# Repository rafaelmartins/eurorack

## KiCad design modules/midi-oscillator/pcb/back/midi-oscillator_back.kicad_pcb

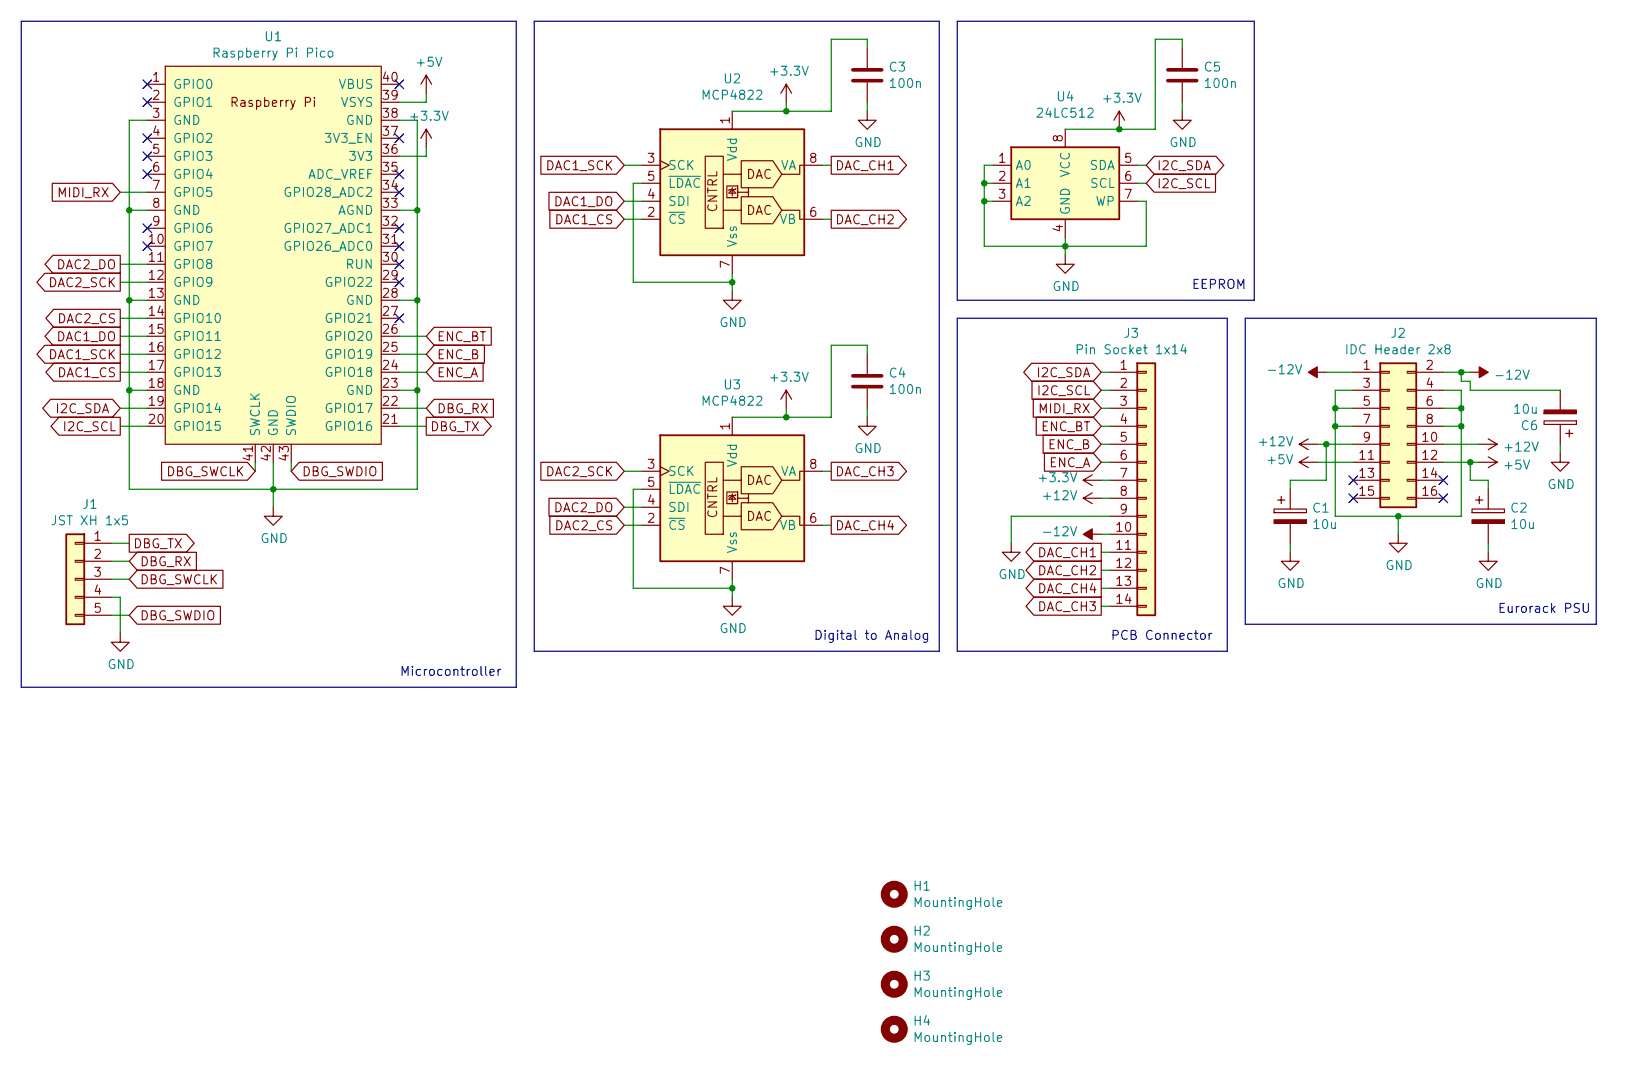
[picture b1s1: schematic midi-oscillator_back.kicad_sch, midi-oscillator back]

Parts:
C1, C2, C6: 10u; CP_Radial_D5.0mm_P2.50mm
C3, C4, C5: 100n; C_Disc_D4.3mm_W1.9mm_P5.00mm
H1, H2, H3, H4: MountingHole; MountingHole_2.2mm_M2
J1: JST XH 1x5; JST_XH_B5B-XH-A_1x05_P2.50mm_Vertical
J2: IDC Header 2x8; IDC-Header_2x08_P2.54mm_Vertical
J3: Pin Socket 1x14; PinSocket_1x14_P2.54mm_Vertical
U1: Raspberry Pi Pico; RPi_Pico_SMD_TH
U2, U3: MCP4822; DIP-8_W7.62mm
U4: 24LC512; DIP-8_W7.62mm

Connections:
+3.3V: C3.1, C4.1, C5.1, J3.7, U1.36 (3V3), U2.1 (Vdd), U3.1 (Vdd), U4.8 (VCC)
+5V: C2.1, J2.11, J2.12, U1.39 (VSYS)
+12V: C1.1, J2.9, J2.10, J3.8
-12V: C6.2, J2.1, J2.2, J3.10
DAC1_CS: U1.17 (GPIO13), U2.2 (~CS)
DAC1_DO: U1.15 (GPIO11), U2.4 (SDI)
DAC1_SCK: U1.16 (GPIO12), U2.3 (SCK)
DAC2_CS: U1.14 (GPIO10), U3.2 (~CS)
DAC2_DO: U1.11 (GPIO8), U3.4 (SDI)
DAC2_SCK: U1.12 (GPIO9), U3.3 (SCK)
DAC_CH1: J3.11, U2.8 (VA)
DAC_CH2: J3.12, U2.6 (VB)
DAC_CH3: J3.14, U3.8 (VA)
DAC_CH4: J3.13, U3.6 (VB)
DBG_RX: J1.2, U1.22 (GPIO17)
DBG_SWCLK: J1.3, U1.41 (SWCLK)
DBG_SWDIO: J1.5, U1.43 (SWDIO)
DBG_TX: J1.1, U1.21 (GPIO16)
ENC_A: J3.6, U1.24 (GPIO18)
ENC_B: J3.5, U1.25 (GPIO19)
ENC_BT: J3.4, U1.26 (GPIO20)
GND: C1.2, C2.2, C3.2, C4.2, C5.2, C6.1, J1.4, J2.3, J2.4, J2.5, J2.6, J2.7, J2.8, J3.9, U1.3 (GND), U1.8 (GND), U1.13 (GND), U1.18 (GND), U1.23 (GND), U1.28 (GND), U1.33 (AGND), U1.38 (GND), U1.42 (GND), U2.5 (~LDAC), U2.7 (Vss), U3.5 (~LDAC), U3.7 (Vss), U4.1 (A0), U4.2 (A1), U4.3 (A2), U4.4 (GND), U4.7 (WP)
I2C_SCL: J3.2, U1.20 (GPIO15), U4.6 (SCL)
I2C_SDA: J3.1, U1.19 (GPIO14), U4.5 (SDA)
MIDI_RX: J3.3, U1.7 (GPIO5)

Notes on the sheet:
EEPROM
PCB Connector
Eurorack PSU
Digital to Analog
Microcontroller

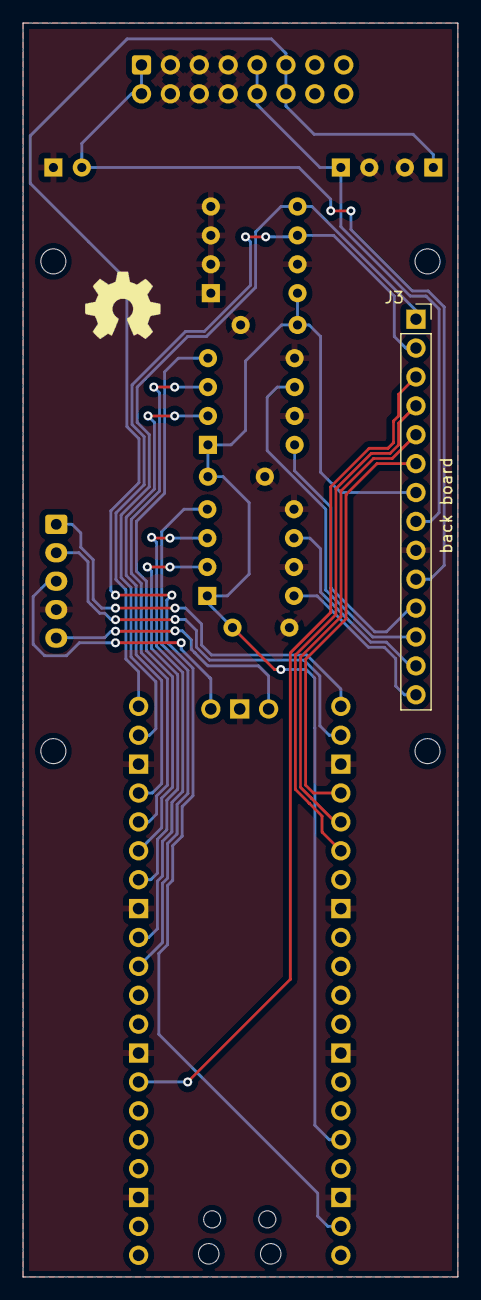
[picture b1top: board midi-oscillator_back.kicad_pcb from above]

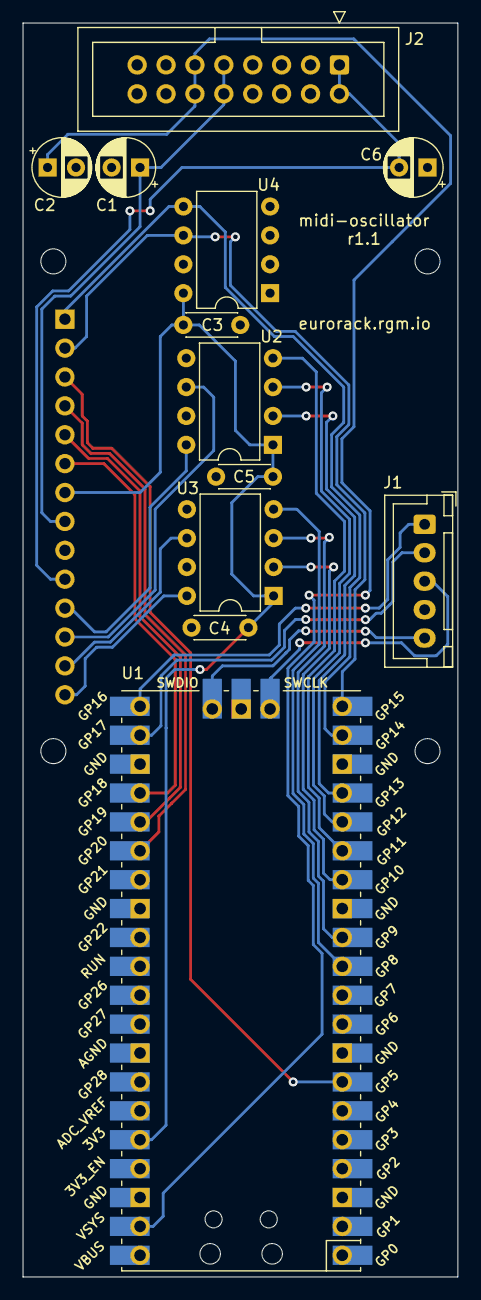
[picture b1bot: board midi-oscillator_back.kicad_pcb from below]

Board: 2 copper layers, 38.2 x 110.2 mm, 17 parts (12 on the bottom side), 25 nets.

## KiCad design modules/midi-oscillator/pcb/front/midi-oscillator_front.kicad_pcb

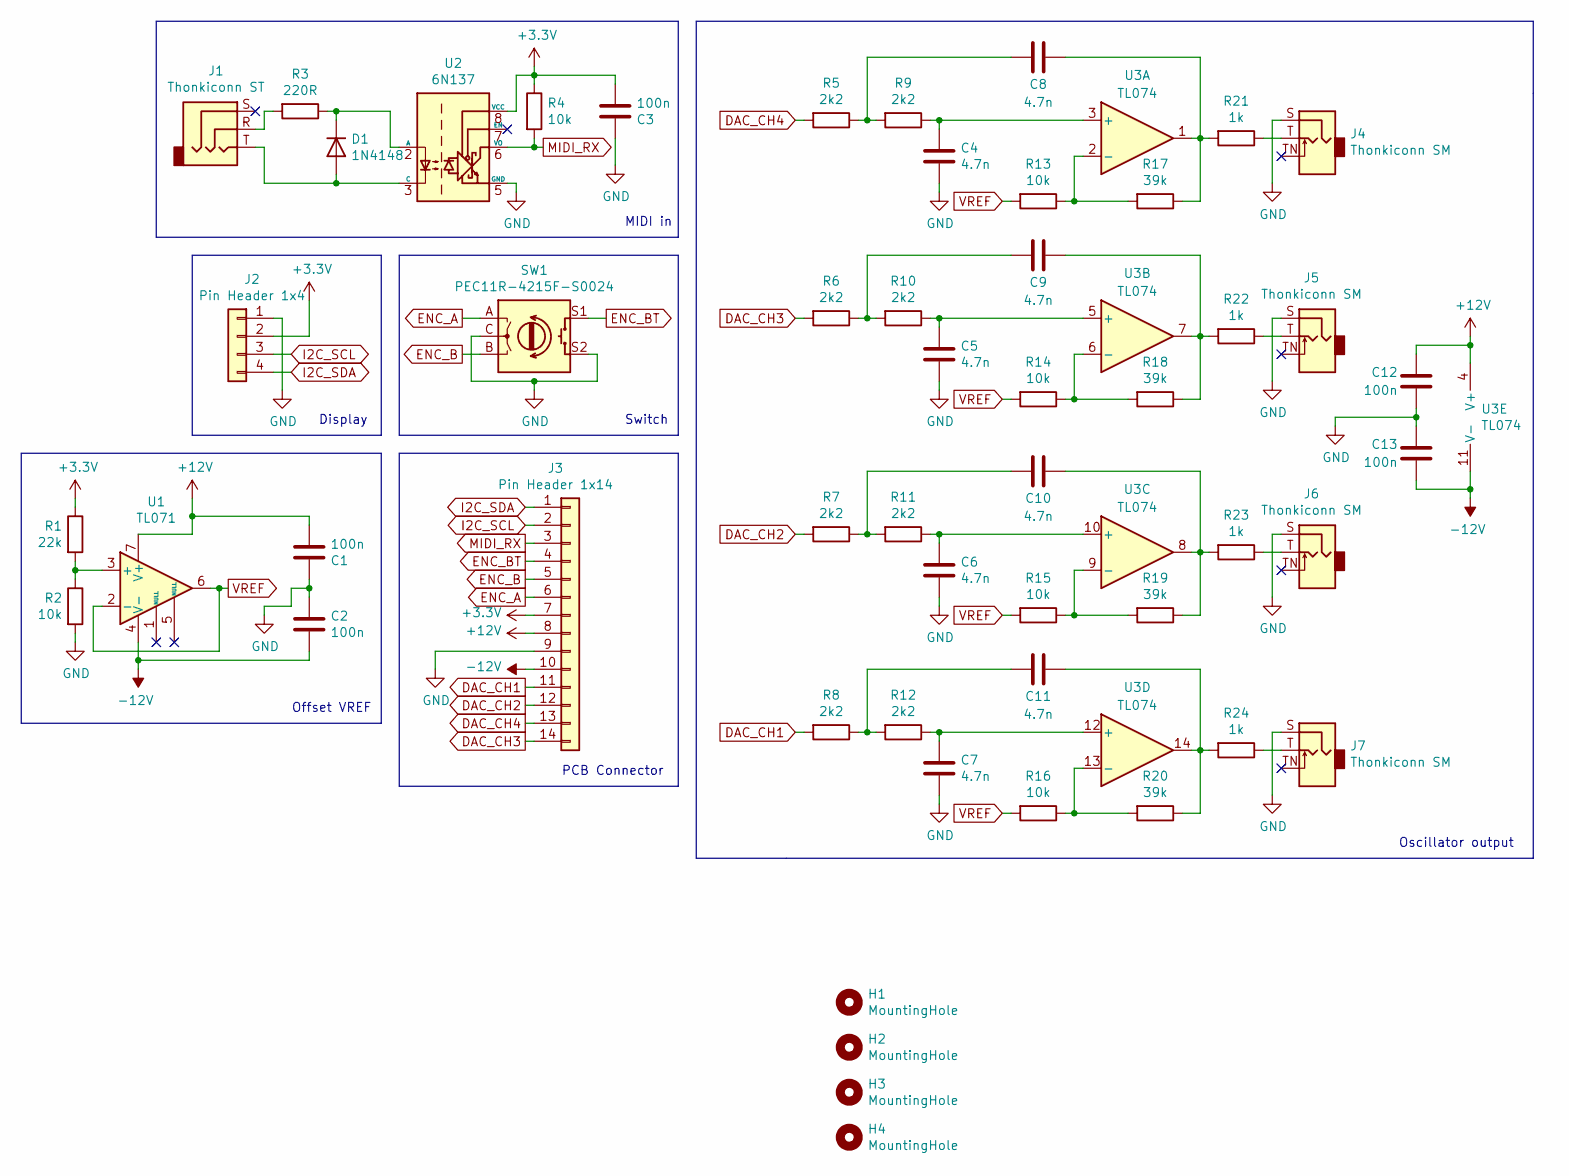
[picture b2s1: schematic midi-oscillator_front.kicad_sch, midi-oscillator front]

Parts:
C1, C2, C3, C12, C13: 100n; C_Disc_D4.3mm_W1.9mm_P5.00mm
C4, C5, C6, C7, C8, C9, C10, C11: 4.7n; C_Rect_L7.0mm_W2.5mm_P5.00mm
D1: 1N4148; D_DO-35_SOD27_P7.62mm_Horizontal
H1, H2, H3, H4: MountingHole; MountingHole_2.2mm_M2
J1: Thonkiconn ST; Jack_3.5mm_QingPu_WQP-PJ366ST_Vertical
J2: Pin Header 1x4; PinSocket_1x04_P2.54mm_Vertical
J3: Pin Header 1x14; PinHeader_1x14_P2.54mm_Vertical
J4, J5, J6, J7: Thonkiconn SM; Jack_3.5mm_QingPu_WQP-PJ398SM_Vertical
R1: 22k; R_Axial_DIN0207_L6.3mm_D2.5mm_P10.16mm_Horizontal
R2, R4, R13, R14, R15, R16: 10k; R_Axial_DIN0207_L6.3mm_D2.5mm_P10.16mm_Horizontal
R3: 220R; R_Axial_DIN0207_L6.3mm_D2.5mm_P10.16mm_Horizontal
R5, R6, R7, R8, R9, R10, R11, R12: 2k2; R_Axial_DIN0207_L6.3mm_D2.5mm_P10.16mm_Horizontal
R17, R18, R19, R20: 39k; R_Axial_DIN0207_L6.3mm_D2.5mm_P10.16mm_Horizontal
R21, R22, R23, R24: 1k; R_Axial_DIN0207_L6.3mm_D2.5mm_P10.16mm_Horizontal
SW1: PEC11R-4215F-S0024; RotaryEncoder_Alps_EC11E-Switch_Vertical_H20mm_CircularMoun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
U1: TL071; DIP-8_W7.62mm
U2: 6N137; DIP-8_W7.62mm
U3: TL074; DIP-14_W7.62mm

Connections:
+3.3V: C3.2, J2.2, J3.7, R1.1, R4.1, U2.8 (VCC)
+12V: C1.2, C12.2, J3.8, U1.7 (V+), U3.4 (V+)
-12V: C2.2, C13.2, J3.10, U1.4 (V-), U3.11 (V-)
DAC_CH1: J3.11, R8.2
DAC_CH2: J3.12, R7.2
DAC_CH3: J3.14, R6.2
DAC_CH4: J3.13, R5.2
ENC_A: J3.6, SW1.A
ENC_B: J3.5, SW1.B
ENC_BT: J3.4, SW1.S1
GND: C1.1, C2.1, C3.1, C4.2, C5.2, C6.2, C7.2, C12.1, C13.1, J2.1, J3.9, J4.S, J5.S, J6.S, J7.S, R2.2, SW1.C, SW1.S2, U2.5 (GND)
I2C_SCL: J2.3, J3.2
I2C_SDA: J2.4, J3.1
MIDI_RX: J3.3, R4.2, U2.6 (VO)
unnamed: C4.1, R9.1, U3.3 (+)
unnamed: C5.1, R10.1, U3.5 (+)
unnamed: C6.1, R11.1, U3.10 (+)
unnamed: C7.1, R12.1, U3.12 (+)
unnamed: C8.1, R5.1, R9.2
unnamed: C8.2, R17.1, R21.2, U3.1
unnamed: C9.1, R6.1, R10.2
unnamed: C9.2, R18.1, R22.2, U3.7
unnamed: C10.1, R7.1, R11.2
unnamed: C10.2, R19.1, R23.2, U3.8
unnamed: C11.1, R8.1, R12.2
unnamed: C11.2, R20.1, R24.2, U3.14
unnamed: D1.1 (K), R3.1, U2.2 (A)
unnamed: D1.2 (A), J1.T, U2.3 (C)
unnamed: J1.R, R3.2
unnamed: J4.T, R21.1
unnamed: J5.T, R22.1
unnamed: J6.T, R23.1
unnamed: J7.T, R24.1
unnamed: R1.2, R2.1, U1.3 (+)
unnamed: R13.1, R17.2, U3.2 (-)
unnamed: R14.1, R18.2, U3.6 (-)
unnamed: R15.1, R19.2, U3.9 (-)
unnamed: R16.1, R20.2, U3.13 (-)
VREF: R13.2, R14.2, R15.2, R16.2, U1.2 (-), U1.6

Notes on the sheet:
Offset VREF
Oscillator output
Switch
Display
PCB Connector
MIDI in

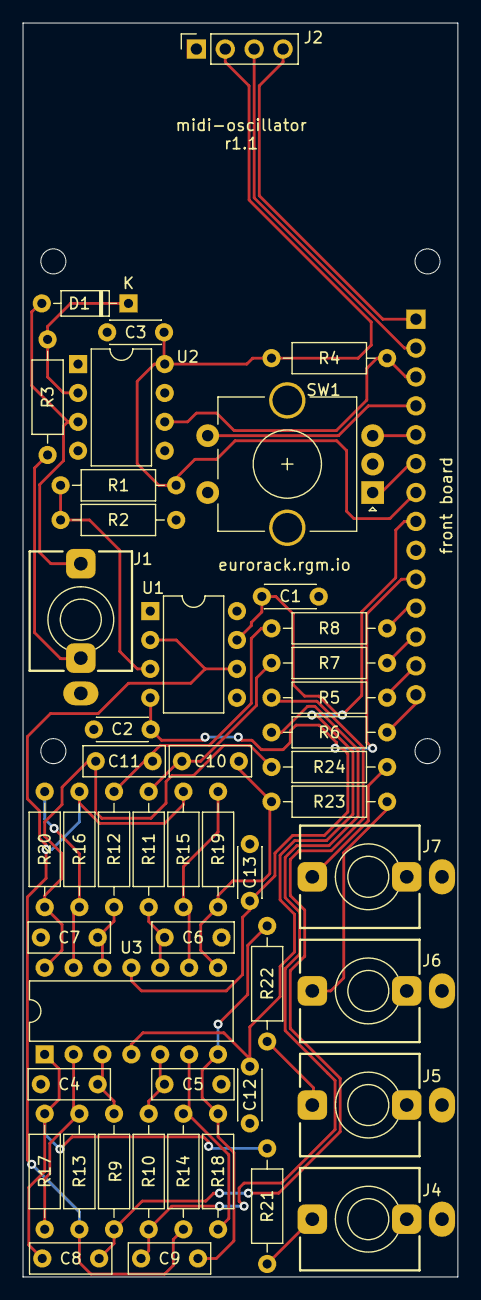
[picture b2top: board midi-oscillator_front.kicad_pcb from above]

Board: 2 copper layers, 38.2 x 110.2 mm, 53 parts (1 on the bottom side), 39 nets.

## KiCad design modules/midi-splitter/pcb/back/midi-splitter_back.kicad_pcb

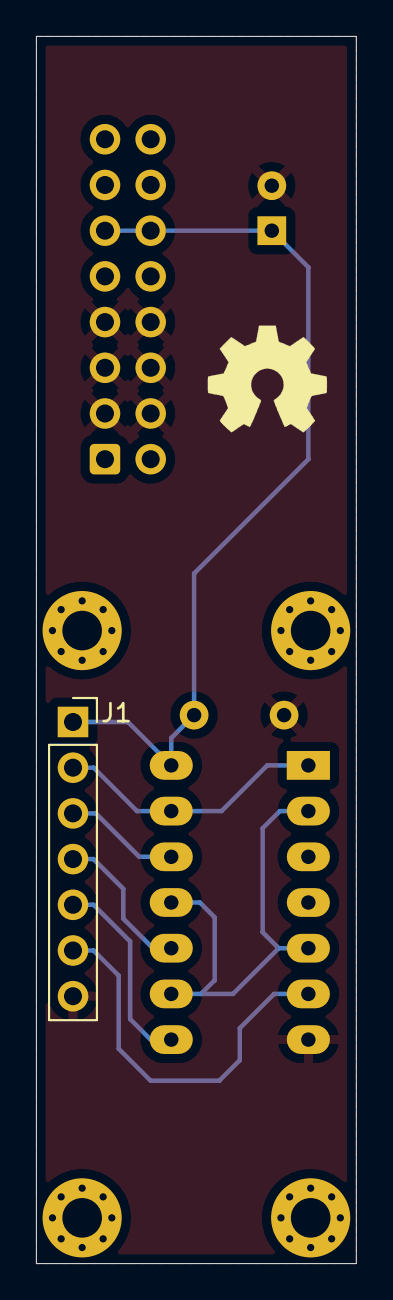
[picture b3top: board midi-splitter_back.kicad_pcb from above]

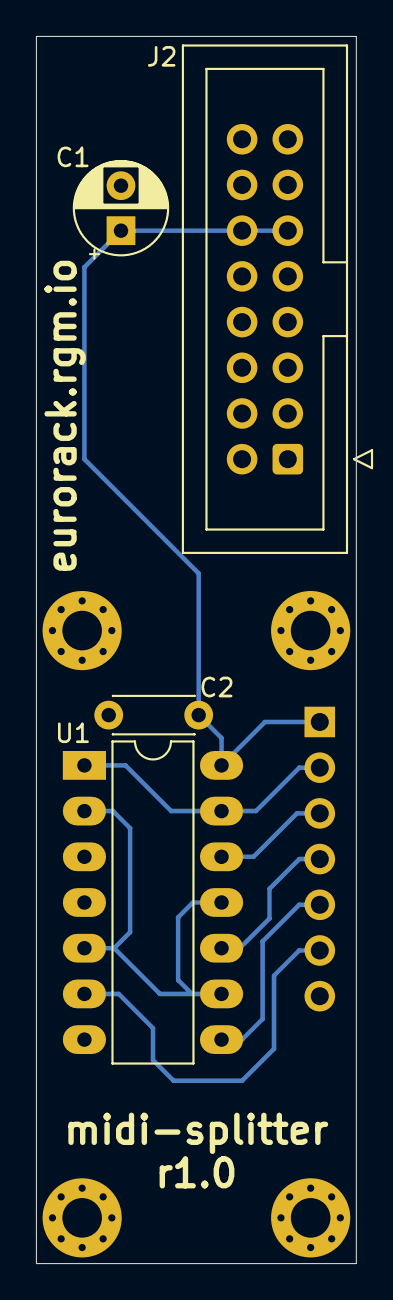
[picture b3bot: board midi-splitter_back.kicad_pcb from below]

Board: 2 copper layers, 17.8 x 68.2 mm, 9 parts (4 on the bottom side), 8 nets.

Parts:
C1: 10u; CP_Radial_D5.0mm_P2.50mm
C2: 100n; C_Disc_D4.3mm_W1.9mm_P5.00mm
H1, H2, H3, H4: MountingHole; MountingHole_2.2mm_M2_Pad_Via
J1: Pin Socket 1x7; PinSocket_1x07_P2.54mm_Vertical
J2: IDC Header 2x8; IDC-Header_2x08_P2.54mm_Vertical
U1: 74HC14; DIP-14_W7.62mm_LongPads

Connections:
+5V: C1.1, C2.1, J1.1, J2.11, J2.12, U1.14 (VCC)
GND: C1.2, C2.2, J1.7, J2.3, J2.4, J2.5, J2.6, J2.7, J2.8, U1.7 (GND)
LED: J1.3, U1.12
MIDI_IN: J1.2, U1.1, U1.13
MIDI_OUT_1: J1.4, U1.10
MIDI_OUT_2: J1.5, U1.8
MIDI_OUT_3: J1.6, U1.6
unnamed: U1.2, U1.5, U1.9, U1.11

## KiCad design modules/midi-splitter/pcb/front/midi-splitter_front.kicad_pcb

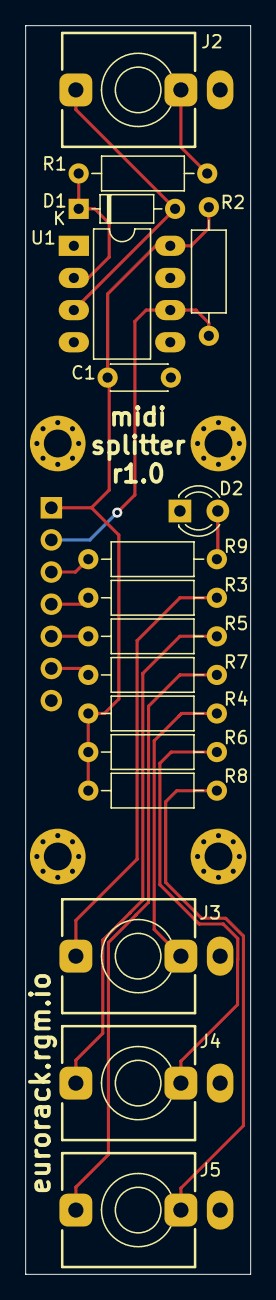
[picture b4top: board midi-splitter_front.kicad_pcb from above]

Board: 2 copper layers, 17.8 x 98.7 mm, 22 parts (1 on the bottom side), 17 nets.

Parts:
C1: 100n; C_Disc_D4.3mm_W1.9mm_P5.00mm
D1: 1N4148; D_DO-35_SOD27_P7.62mm_Horizontal
D2: LED; LED_D3.0mmP2.54mm
H1, H2, H3, H4: MountingHole; MountingHole_2.2mm_M2_Pad_Via
J1: Pin Header 1x7; PinHeader_1x07_P2.54mm_Vertical
J2, J3, J4, J5: Thonkiconn ST; Jack_3.5mm_QingPu_WQP-PJ366ST_Vertical
R1, R3, R4, R5, R6, R7, R8: 220R; R_Axial_DIN0207_L6.3mm_D2.5mm_P10.16mm_Horizontal
R2: 10k; R_Axial_DIN0207_L6.3mm_D2.5mm_P10.16mm_Horizontal
R9: 2k2; R_Axial_DIN0207_L6.3mm_D2.5mm_P10.16mm_Horizontal
U1: 6N137; DIP-8_W7.62mm_LongPads

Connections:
+5V: C1.1, J1.1, R2.1, R4.1, R6.1, R8.1, U1.8 (VCC)
GND: C1.2, D2.1 (K), J1.7, J3.S, J4.S, J5.S, U1.5 (GND)
LED: J1.3, R9.1
MIDI_IN: J1.2, R2.2, U1.6 (VO)
MIDI_OUT_1: J1.4, R3.1
MIDI_OUT_2: J1.5, R5.1
MIDI_OUT_3: J1.6, R7.1
unnamed: D1.1 (K), R1.2, U1.2 (A)
unnamed: D1.2 (A), J2.T, U1.3 (C)
unnamed: D2.2 (A), R9.2
unnamed: J2.R, R1.1
unnamed: J3.R, R4.2
unnamed: J3.T, R3.2
unnamed: J4.R, R6.2
unnamed: J4.T, R5.2
unnamed: J5.R, R8.2
unnamed: J5.T, R7.2

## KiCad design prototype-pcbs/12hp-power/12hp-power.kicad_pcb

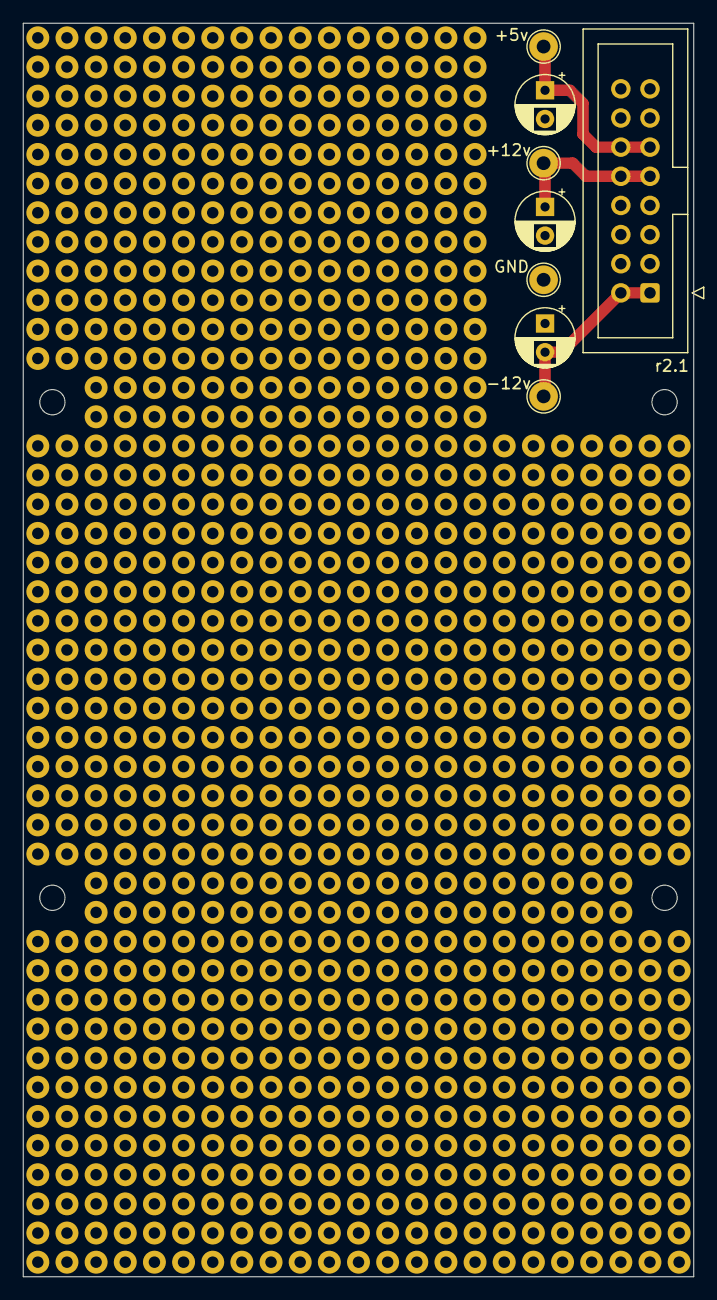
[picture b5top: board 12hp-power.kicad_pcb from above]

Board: 2 copper layers, 58.4 x 109.2 mm, 8 parts (0 on the bottom side), 4 nets.

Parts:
C1, C2, C3: CP; CP_Radial_D5.0mm_P2.50mm
J1: IDC Header 2x8; IDC-Header_2x08_P2.54mm_Vertical
TP1: +5v; TestPoint_THTPad_D2.5mm_Drill1.2mm
TP2: +12v; TestPoint_THTPad_D2.5mm_Drill1.2mm
TP3: GND; TestPoint_THTPad_D2.5mm_Drill1.2mm
TP4: -12v; TestPoint_THTPad_D2.5mm_Drill1.2mm

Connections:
+5V: C1.1, J1.11, J1.12, TP1.1
+12V: C2.1, J1.9, J1.10, TP2.1
-12V: C3.2, J1.1, J1.2, TP4.1
GND: C1.2, C2.2, C3.1, J1.3, J1.4, J1.5, J1.6, J1.7, J1.8, TP3.1

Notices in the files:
modules/midi-oscillator/pcb/back/midi-oscillator_back.kicad_sch:
Released under CERN Open Hardware Licence Version 2 - Strongly Reciprocal
